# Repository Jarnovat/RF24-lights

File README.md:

# RF24-lights
nRF24L01+ network to control lights

More info of the project at:

https://hackaday.io/project/8155-nrf24l01-network-to-control-lights

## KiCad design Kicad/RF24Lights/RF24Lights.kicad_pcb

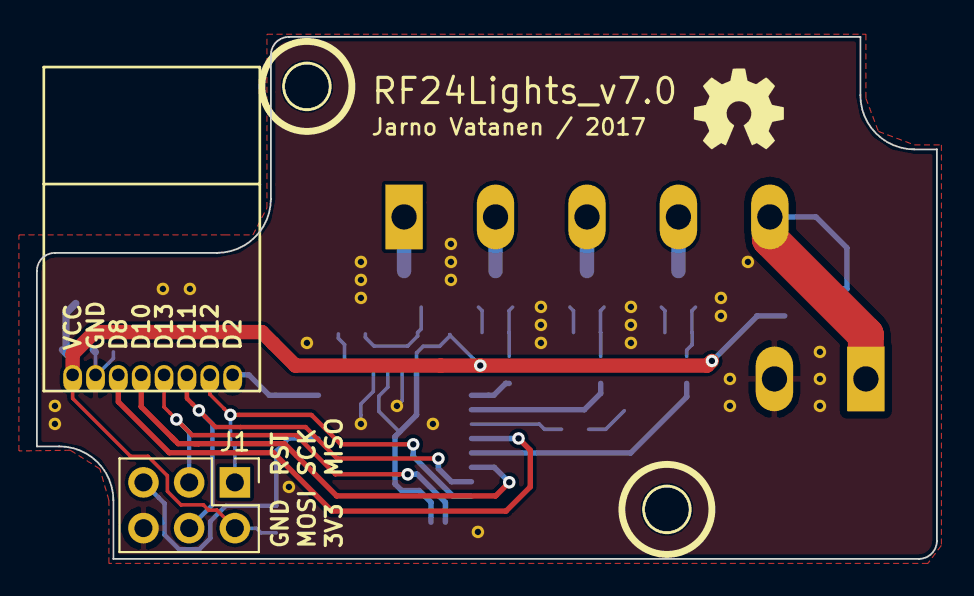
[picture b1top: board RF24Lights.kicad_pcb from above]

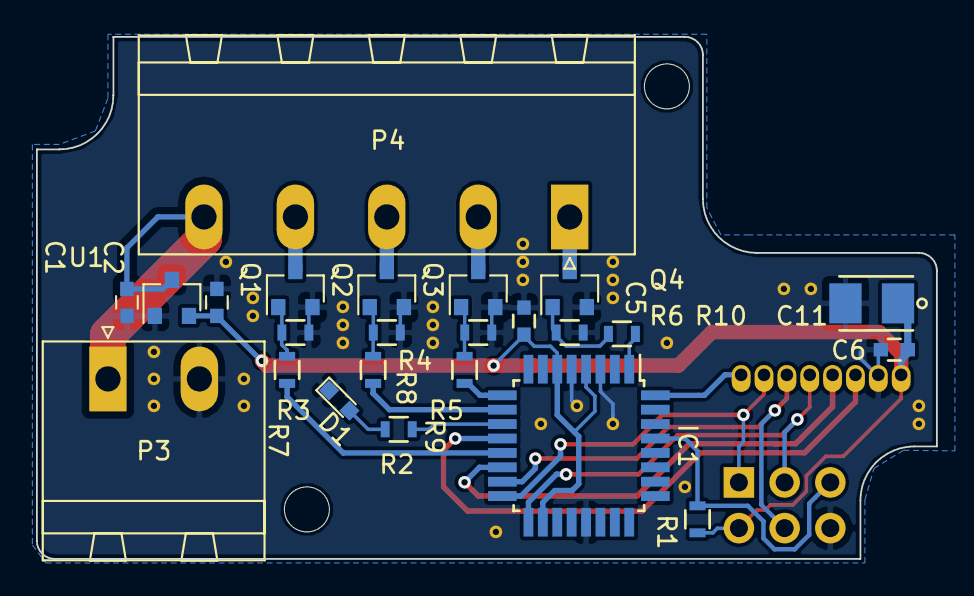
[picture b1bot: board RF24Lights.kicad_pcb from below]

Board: 2 copper layers, 50.0 x 29.0 mm, 26 parts (24 on the bottom side), 24 nets.

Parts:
C1: 1uF; C_0603
C2: 2,2uF; C_0603
C5, C6: C; C_0603
C11: 10uF; TantalC_SizeB_EIA-3528_Reflow_Polar
D1: LED; LED_0603
IC1: ATMEGA328-A; TQFP-32_7x7mm_Pitch0.8mm
J1: CONN_02X03; Pin_Header_Straight_2x03_Pitch2.54mm
P3: CONN_01X02; PhoenixContact_MSTBA-G_02x5.08mm_Angled
P4: CONN_01X05; PhoenixContact_MSTBA-G_05x5.08mm_Angled
P5: CONN_01X08; nrf24l01_mini
Q1, Q2, Q3, Q4: BSS138; SOT-23
R1, R3, R4, R5, R6: 10K; R_0603
R2, R7, R8, R9, R10: R; R_0603
U1: AP2210; SOT-23

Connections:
+3V3: C2.1, C5.1, C6.2, C11.1, IC1.4, IC1.6, IC1.18, J1.2, P5.1, R1.1, U1.2
+12V: C1.1, P3.1, P4.5, U1.3
/D2: IC1.32, P5.8
/D8: IC1.12, P5.3
/D10: IC1.14, P5.4
/D11: IC1.15, J1.4, P5.6
/D12: IC1.16, J1.1, P5.7
/D13: IC1.17, J1.3, P5.5
/LED: IC1.11, R2.2
/OUT1: P4.4, Q1.3
/OUT2: P4.3, Q2.3
/OUT3: P4.2, Q3.3
/OUT4: P4.1, Q4.3
/PWM1: IC1.13, R7.2
/PWM2: IC1.10, R8.2
/PWM3: IC1.9, R9.2
/PWM4: IC1.1, R10.2
/RST: IC1.29, J1.5, R1.2
GND: C1.2, C2.2, C5.2, C6.1, C11.2, D1.1, IC1.3, IC1.5, IC1.21, J1.6, P3.2, P5.2, Q1.2, Q2.2, Q3.2, Q4.2, R3.1, R4.1, R5.1, R6.1, U1.1
unnamed: D1.2, R2.1
unnamed: Q1.1, R3.2, R7.1
unnamed: Q2.1, R4.2, R8.1
unnamed: Q3.1, R5.2, R9.1
unnamed: Q4.1, R6.2, R10.1

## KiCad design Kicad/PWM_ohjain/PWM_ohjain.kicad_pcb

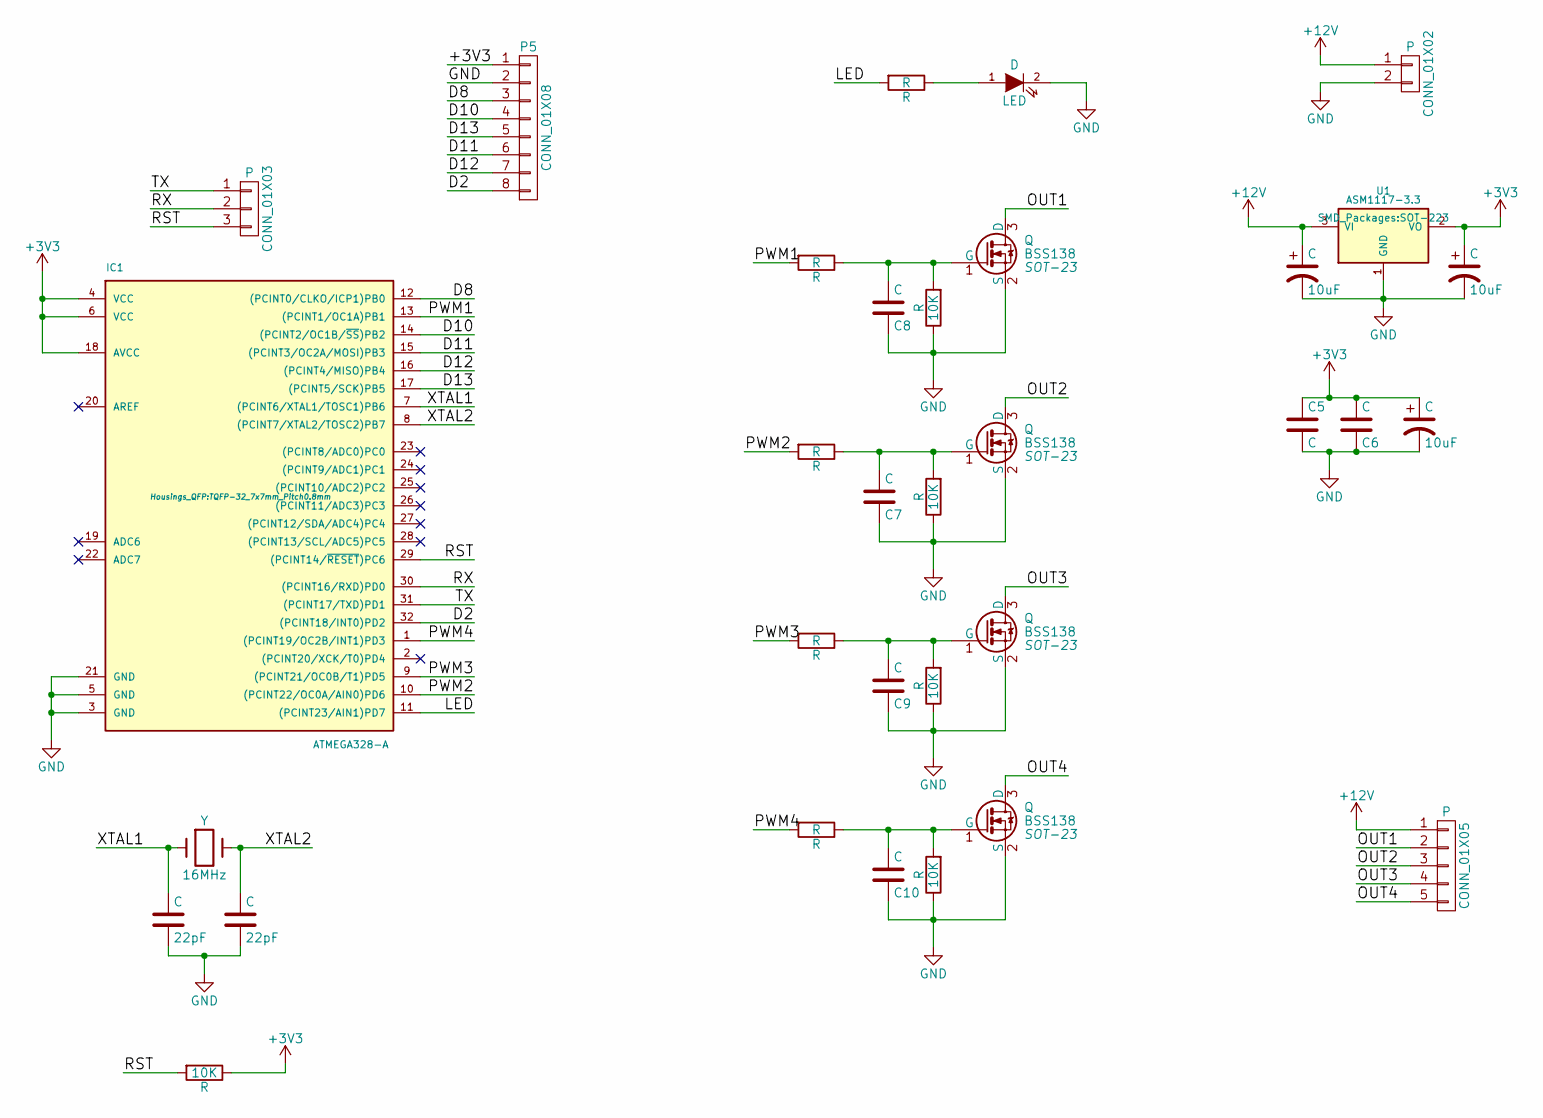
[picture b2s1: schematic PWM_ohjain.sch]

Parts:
C1, C2: 22pF; C_0603
C3, C4, C11: 10uF; TantalC_SizeB_EIA-3528_Reflow_Polar
C5, C6, C7, C8, C9, C10: C; C_0603
D1: LED; LED-0603
IC1: ATMEGA328-A; TQFP-32_7x7mm_Pitch0.8mm
P1: CONN_01X03; Pin_Header_Straight_1x03
P3: CONN_01X02; Terminal_Block_2pin_RuggedPads
P4: CONN_01X05; Terminal_Block_5pin_RuggedPads
P5: CONN_01X08; nrf24l01_mini
Q1, Q2, Q3, Q4: BSS138; SOT-23
R1, R3, R4, R5, R6: 10K; R_0603
R2, R7, R8, R9, R10: R; R_0603
U1: ASM1117-3.3; SOT-223
Y1: 16MHz; Crystal_HC49-SD_SMD

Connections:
+3V3: C4.1, C5.1, C6.2, C11.1, IC1.4 (VCC), IC1.6 (VCC), IC1.18 (AVCC), P5.1, R1.1, U1.2 (VO)
+12V: C3.1, P3.1, P4.1, U1.3 (VI)
/D2: IC1.32 ((PCINT18/INT0)PD2), P5.8
/D8: IC1.12 ((PCINT0/CLKO/ICP1)PB0), P5.3
/D10: IC1.14 ((PCINT2/OC1B/~SS~)PB2), P5.4
/D11: IC1.15 ((PCINT3/OC2A/MOSI)PB3), P5.6
/D12: IC1.16 ((PCINT4/MISO)PB4), P5.7
/D13: IC1.17 ((PCINT5/SCK)PB5), P5.5
/LED: IC1.11 ((PCINT23/AIN1)PD7), R2.2
/OUT1: P4.2, Q1.3 (D)
/OUT2: P4.3, Q2.3 (D)
/OUT3: P4.4, Q3.3 (D)
/OUT4: P4.5, Q4.3 (D)
/PWM1: IC1.13 ((PCINT1/OC1A)PB1), R7.2
/PWM2: IC1.10 ((PCINT22/OC0A/AIN0)PD6), R8.2
/PWM3: IC1.9 ((PCINT21/OC0B/T1)PD5), R9.2
/PWM4: IC1.1 ((PCINT19/OC2B/INT1)PD3), R10.2
/RST: IC1.29 ((PCINT14/~RESET~)PC6), P1.3, R1.2
/RX: IC1.30 ((PCINT16/RXD)PD0), P1.2
/TX: IC1.31 ((PCINT17/TXD)PD1), P1.1
/XTAL1: C1.1, IC1.7 ((PCINT6/XTAL1/TOSC1)PB6), Y1.1
/XTAL2: C2.1, IC1.8 ((PCINT7/XTAL2/TOSC2)PB7), Y1.2
GND: C1.2, C2.2, C3.2, C4.2, C5.2, C6.1, C7.1, C8.1, C9.1, C10.1, C11.2, D1.2 (K), IC1.3 (GND), IC1.5 (GND), IC1.21 (GND), P3.2, P5.2, Q1.2 (S), Q2.2 (S), Q3.2 (S), Q4.2 (S), R3.1, R4.1, R5.1, R6.1, U1.1 (GND)
unnamed: C7.2, Q2.1 (G), R4.2, R8.1
unnamed: C8.2, Q1.1 (G), R3.2, R7.1
unnamed: C9.2, Q3.1 (G), R5.2, R9.1
unnamed: C10.2, Q4.1 (G), R6.2, R10.1
unnamed: D1.1 (A), R2.1

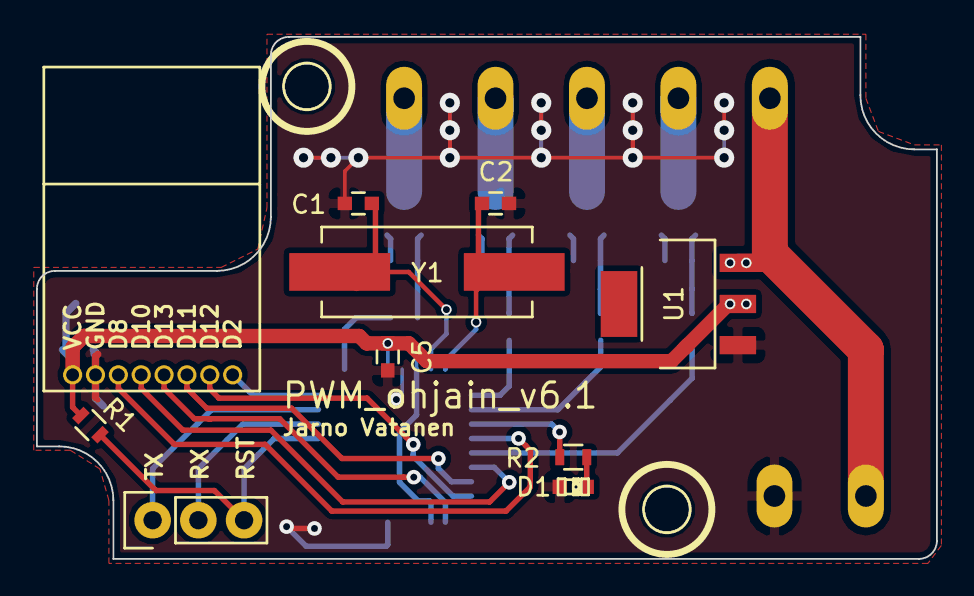
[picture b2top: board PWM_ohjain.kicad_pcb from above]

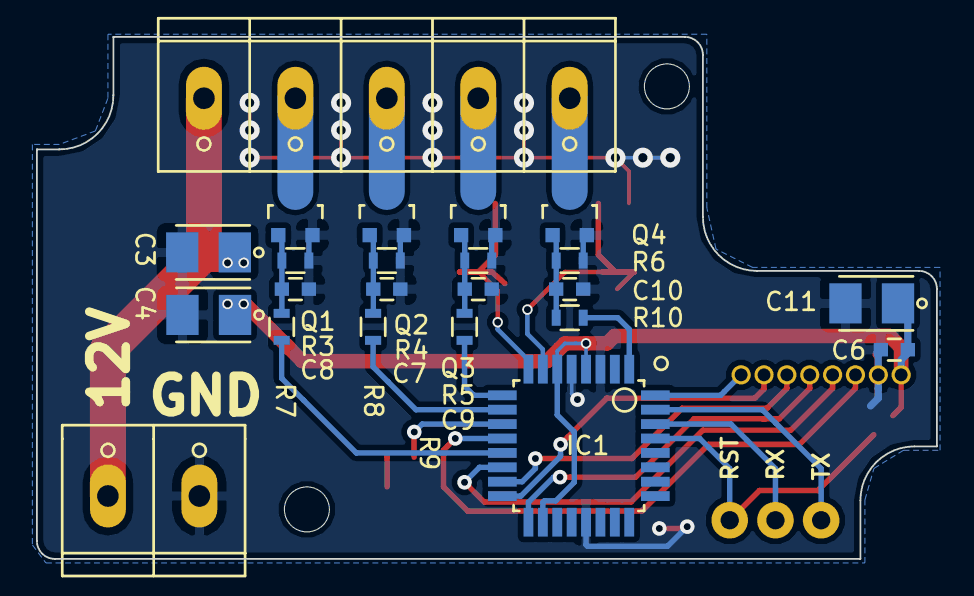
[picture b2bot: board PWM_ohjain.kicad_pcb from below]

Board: 2 copper layers, 50.0 x 29.0 mm, 33 parts (23 on the bottom side), 28 nets.

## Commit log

2015-10-29 Modified the indentation.
2015-10-29 Kicad files for the receiver unit
2015-10-29 Code for the server
2015-10-29 Added link to hackaday.io
2015-11-09 Fixed a bug in the BTserial reading
    Upped the speed of BTSerial and changed the way how it buffers the
    incoming serial data. Now it can receive data faster.
2015-11-21 Added android source code and .apk
    The app has some bugs and is still experimental.
2017-08-26 New version of PWM_ohjain
    New version of receiver PCB, Name changed at the same time
2017-08-26 Library files for RF24Lights
